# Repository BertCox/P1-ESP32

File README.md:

# P1-ESP32
P1-port reader connected to a ESP32 for smart meters in Belgium. This design is based on the P1-to-ethernet board of [Marcel Zuidwijk](https://www.zuidwijk.com/p1-to-ethernet/).

## Hardware used:
- ESP32 DEV KIT V1. You can buy [here](https://nl.aliexpress.com/item/1005008127727230.html?spm=a2g0o.productlist.main.1.725aOsrrOsrrnR&algo_pvid=d06b4777-2f12-4753-9c76-e8a9cc5e704a&algo_exp_id=d06b4777-2f12-4753-9c76-e8a9cc5e704a-0&pdp_ext_f=%7B%22order%22%3A%2282%22%2C%22eval%22%3A%221%22%7D&pdp_npi=6%40dis%21EUR%215.52%213.59%21%21%2144.88%2129.19%21%40211b80c217562076904564345e3b5a%2112000043901420260%21sea%21BE%210%21ABX%211%210%21n_tag%3A-29910%3Bd%3Ad1cb1d89%3Bm03_new_user%3A-29895&curPageLogUid=An5AY2Hn4jBK&utparam-url=scene%3Asearch%7Cquery_from%3A%7Cx_object_id%3A1005008127727230%7C_p_origin_prod%3A) and find the corresponding footprint [here](https://gitlab.com/VictorLamoine/kicad/-/tree/5?ref_type=heads).
- BSS138 in SOT23 package
- J12 connector, which you can buy [here](https://www.mouser.be/ProductDetail/Wurth-Elektronik/615006138421?qs=rS3zZhy2AQPoaD7M%2F0wyLg%3D%3D)

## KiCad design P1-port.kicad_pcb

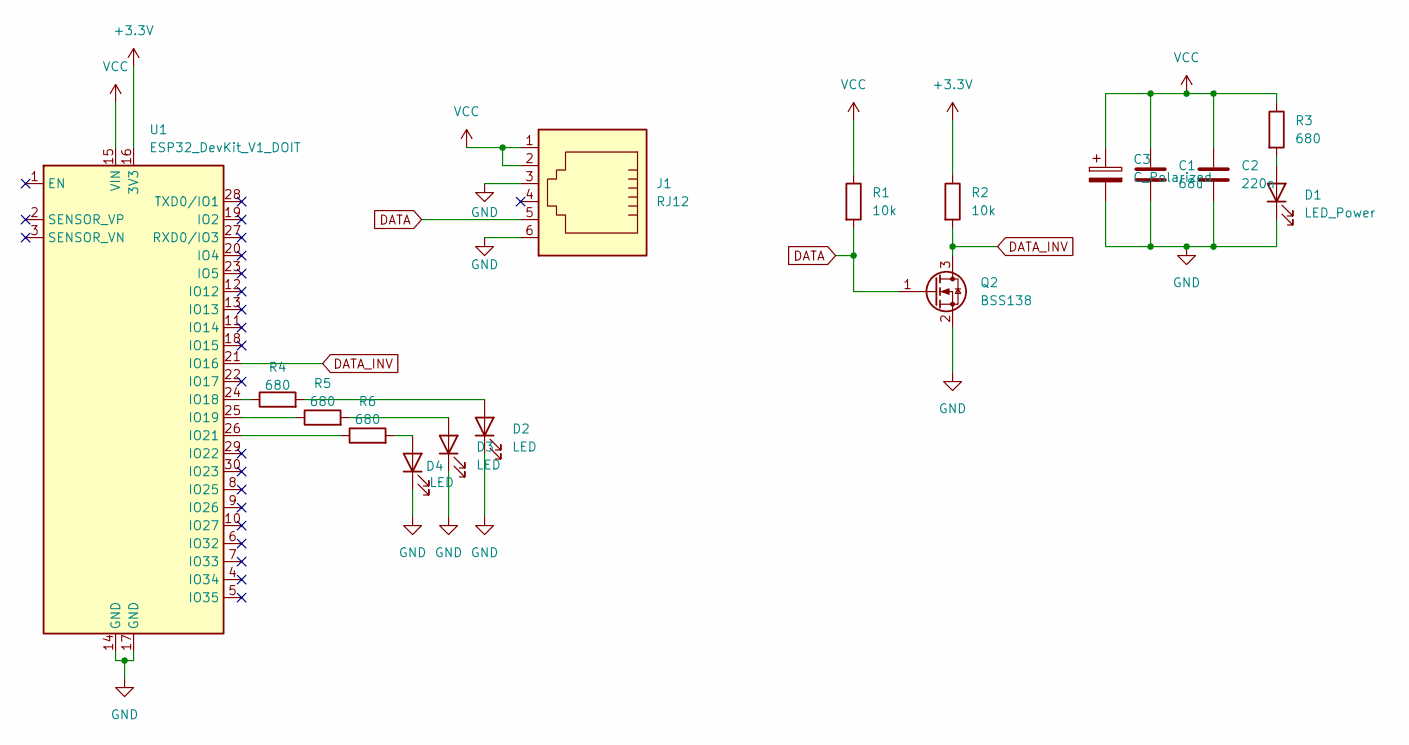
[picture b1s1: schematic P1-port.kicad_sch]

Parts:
C1: 68u; C_0805_2012Metric_Pad1.18x1.45mm_HandSolder
C2: 220n; C_0805_2012Metric_Pad1.18x1.45mm_HandSolder
C3: C_Polarized; CP_Radial_D5.0mm_P2.50mm
D1: LED_Power; LED_D5.0mm
D2, D3, D4: LED; LED_D5.0mm
J1: RJ12; 615006138421
Q2: BSS138; SOT-23
R1, R2: 10k; R_0805_2012Metric_Pad1.20x1.40mm_HandSolder
R3, R4, R5, R6: 680; R_0805_2012Metric_Pad1.20x1.40mm_HandSolder
U1: ESP32_DevKit_V1_DOIT; esp32_devkit_v1_doit

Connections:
+3.3V: R2.1, U1.16 (3V3)
DATA: J1.5, Q2.1 (G), R1.2
DATA_INV: Q2.3 (D), R2.2, U1.21 (IO16)
GND: C1.2, C2.2, C3.2, D1.1 (K), D2.1 (K), D3.1 (K), D4.1 (K), J1.3, J1.6, Q2.2 (S), U1.14 (GND), U1.17 (GND)
unnamed: D1.2 (A), R3.2
unnamed: D2.2 (A), R4.2
unnamed: D3.2 (A), R5.2
unnamed: D4.2 (A), R6.2
unnamed: R4.1, U1.24 (IO18)
unnamed: R5.1, U1.25 (IO19)
unnamed: R6.1, U1.26 (IO21)
VCC: C1.1, C2.1, C3.1, J1.1, J1.2, R1.1, R3.1, U1.15 (VIN)

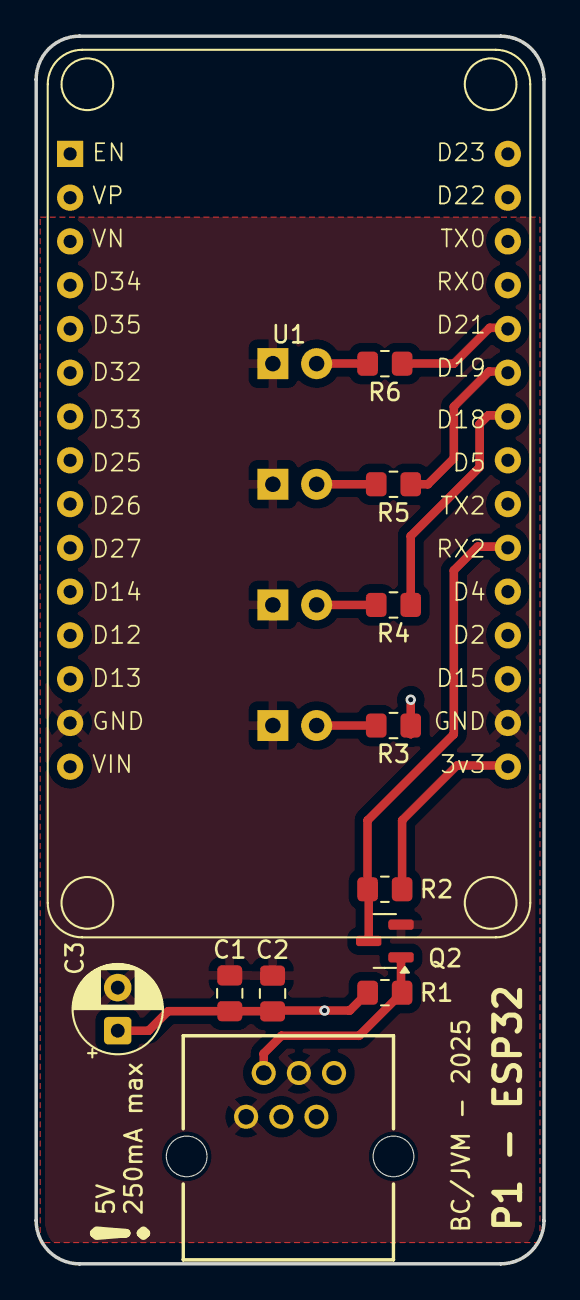
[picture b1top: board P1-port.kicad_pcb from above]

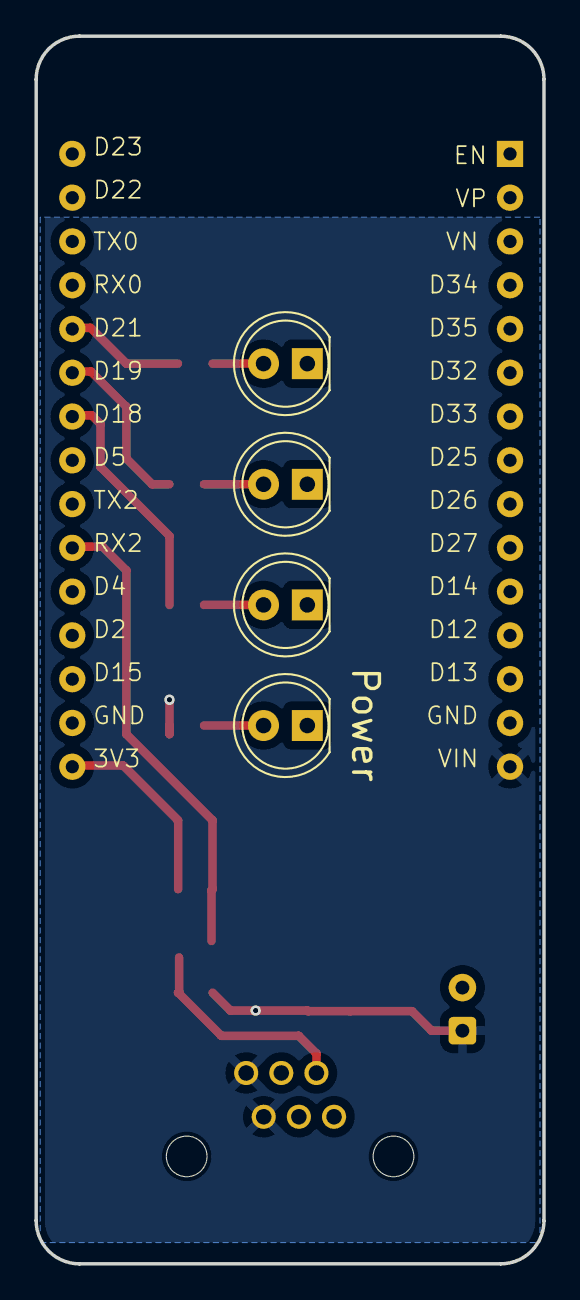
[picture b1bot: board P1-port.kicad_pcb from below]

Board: 2 copper layers, 29.5 x 71.2 mm, 16 parts (4 on the bottom side), 12 nets.

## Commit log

2025-08-26 Added initial files
